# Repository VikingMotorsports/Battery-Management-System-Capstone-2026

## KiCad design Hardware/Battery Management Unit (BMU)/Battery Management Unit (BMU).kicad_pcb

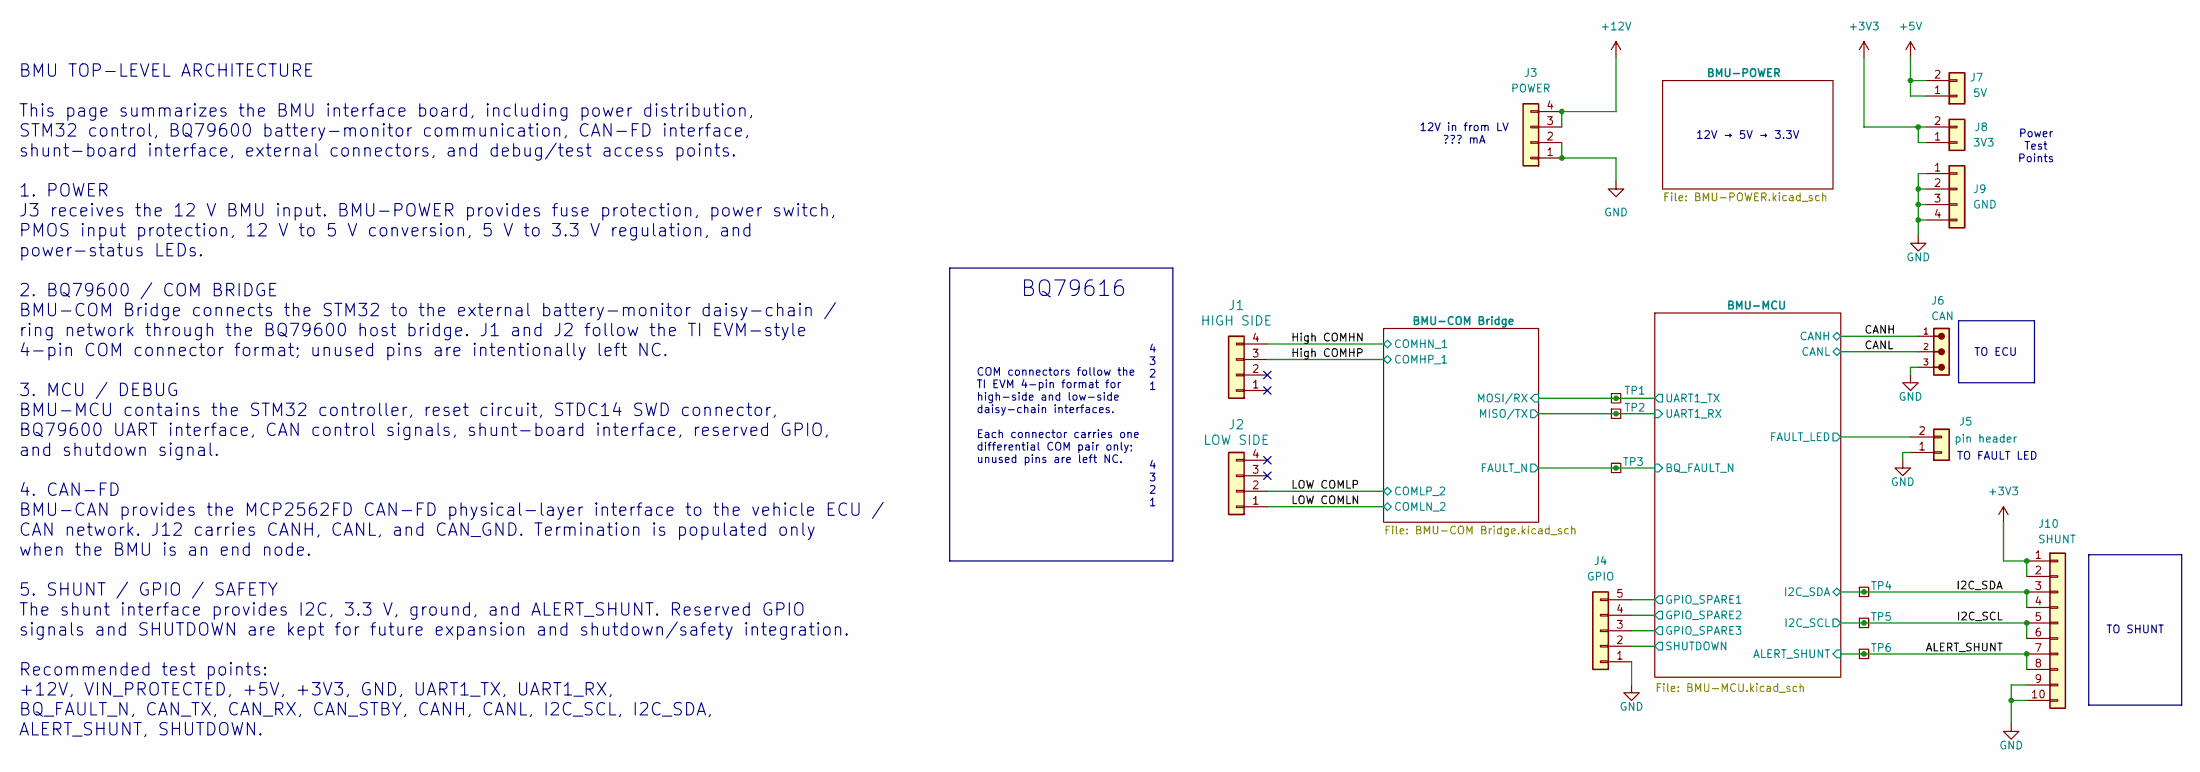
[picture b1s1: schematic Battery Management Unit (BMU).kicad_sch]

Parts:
J1: HIGH SIDE; 705510038; MPN 705510038
J2: LOW SIDE; 705510038; MPN 705510038
J3: POWER; PinHeader_1x04_P2.54mm_Vertical; MPN PRPC004SAAN-RC
J4: GPIO; PinHeader_1x05_P2.54mm_Vertical; MPN PRPC005SAAN-RC
J5: pin header; PinHeader_1x02_P2.54mm_Vertical; MPN PRPC002SAAN-RC
J6: CAN; 691382000003; MPN 691382000003
J7: 5V; PinHeader_1x02_P2.54mm_Vertical; MPN PRPC002SAAN-RC
J8: 3V3; PinHeader_1x02_P2.54mm_Vertical; MPN PRPC002SAAN-RC
J9: GND; PinHeader_1x04_P2.54mm_Vertical; MPN PRPC004SAAN-RC
J10: SHUNT; PinHeader_1x10_P2.54mm_Vertical; MPN PRPC010SAAN-RC
TP1, TP2, TP3, TP4, TP5, TP6: TestPoint_Small; TestPoint_THTPad_D1.5mm_Drill0.7mm

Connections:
+3V3: J8.1, J8.2, J10.1, J10.2; also elsewhere on the board
+5V: J7.1, J7.2; also elsewhere on the board
+12V: J3.3, J3.4; also elsewhere on the board
/ALERT_SHUNT: J10.7, J10.8, TP6.1 (1_1); also elsewhere on the board
/BMU-COM Bridge/FAULT_N: TP3.1 (1_1); also elsewhere on the board
/BMU-COM Bridge/MISO/TX: TP2.1 (1_1); also elsewhere on the board
/BMU-COM Bridge/MOSI/RX: TP1.1 (1_1); also elsewhere on the board
/BMU-MCU/FAULT_LED: J5.2; also elsewhere on the board
/BMU-MCU/GPIO_SPARE1: J4.5; also elsewhere on the board
/BMU-MCU/GPIO_SPARE2: J4.4; also elsewhere on the board
/BMU-MCU/GPIO_SPARE3: J4.3; also elsewhere on the board
/BMU-MCU/SHUTDOWN: J4.2; also elsewhere on the board
/CANH: J6.1; also elsewhere on the board
/CANL: J6.2; also elsewhere on the board
/High COMHN: J1.4; also elsewhere on the board
/High COMHP: J1.3; also elsewhere on the board
/I2C_SCL: J10.5, J10.6, TP5.1 (1_1); also elsewhere on the board
/I2C_SDA: J10.3, J10.4, TP4.1 (1_1); also elsewhere on the board
/LOW COMLN: J2.1; also elsewhere on the board
/LOW COMLP: J2.2; also elsewhere on the board
GND: J3.1, J3.2, J4.1, J5.1, J6.3, J9.1, J9.2, J9.3, J9.4, J10.9, J10.10; also elsewhere on the board

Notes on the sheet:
4 3 2 1
12V in from LV ??? mA
TO FAULT LED
COM connectors follow the TI EVM 4-pin format for high-side and low-side daisy-chain interfaces. Each connector carries one differential COM pair only; unused pins are left NC.
Power Test Points
TO ECU
BMU TOP-LEVEL ARCHITECTURE This page summarizes the BMU interface board, including power distribution, STM32 control, BQ79600 battery-monitor communication, CAN-FD interface, shunt-board interface, external connectors, and debug/test access points. 1. POWER J3 receives the 12 V BMU input. BMU-POWER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
TO SHUNT
12V → 5V → 3.3V
BQ79616

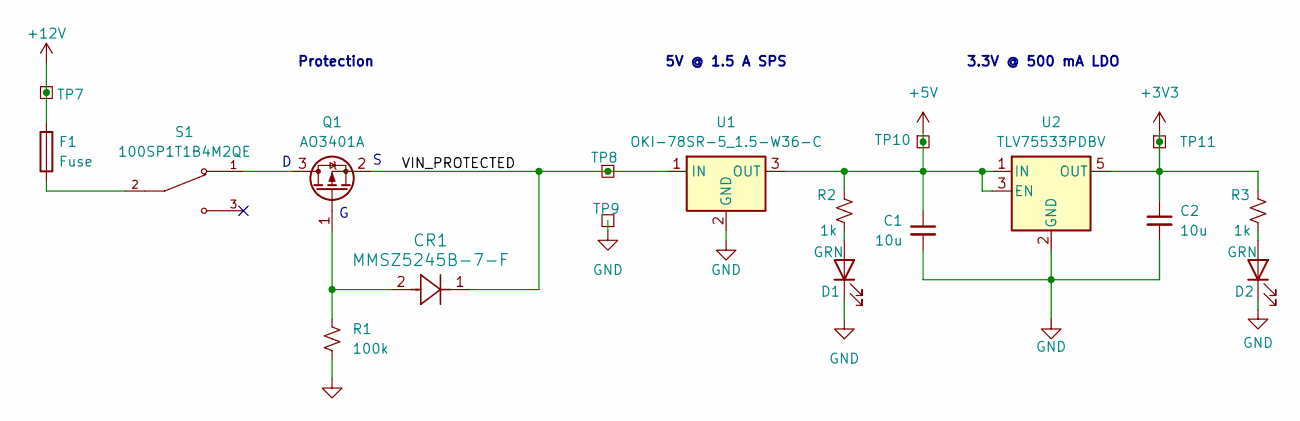
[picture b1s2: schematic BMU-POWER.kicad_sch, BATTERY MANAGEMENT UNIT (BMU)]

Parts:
C1, C2: 10u; C_0805_2012Metric; MPN CC0805KKX5R8BB106
CR1: MMSZ5245B-7-F; SOD123_DIO; MPN MMSZ5245B-7-F
D1, D2: GRN; LED_0805_2012Metric_Pad1.15x1.40mm_HandSolder; MPN LTST-C170GKT
F1: Fuse; Fuse_1206_3216Metric; MPN 0466001.NR
Q1: AO3401A; SOT-23; MPN AO3401A
R1: 100k; R_0805_2012Metric; MPN RC0805FR-07100KL
R2, R3: 1k; R_0805_2012Metric; MPN RC0805FR-071KL
S1: 100SP1T1B4M2QE; SW_100SP1T1B4M2QE; PARTREV E
TP7, TP8, TP9, TP10, TP11: TestPoint_Small; TestPoint_THTPad_D1.5mm_Drill0.7mm
U1: OKI-78SR-5_1.5-W36-C; Converter_DCDC_Murata_OKI-78SR_Vertical; MPN OKI-78SR-5/1.5-W36-C
U2: TLV75533PDBV; SOT-23-5; MPN TLV75533PDBVR

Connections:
+3V3: C2.1, R3.2, TP11.1 (1_1), U2.5 (OUT); also elsewhere on the board
+5V: C1.1, R2.2, TP10.1 (1_1), U1.3 (OUT), U2.1 (IN), U2.3 (EN); also elsewhere on the board
+12V: F1.2, TP7.1 (1_1); also elsewhere on the board
/BMU-POWER/VIN_PROTECTED: CR1.1, Q1.2 (S), TP8.1 (1_1), U1.1 (IN)
GND: C1.2, C2.2, D1.1 (K), D2.1 (K), R1.2, TP9.1 (1_1), U1.2 (GND), U2.2 (GND); also elsewhere on the board
unnamed: D1.2 (A), R2.1
unnamed: D2.2 (A), R3.1
unnamed: F1.1, S1.2
unnamed: Q1.3 (D), S1.1
unnamed: CR1.2, Q1.1 (G), R1.1

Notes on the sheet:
3.3V @ 500 mA LDO
5V @ 1.5 A SPS
Protection

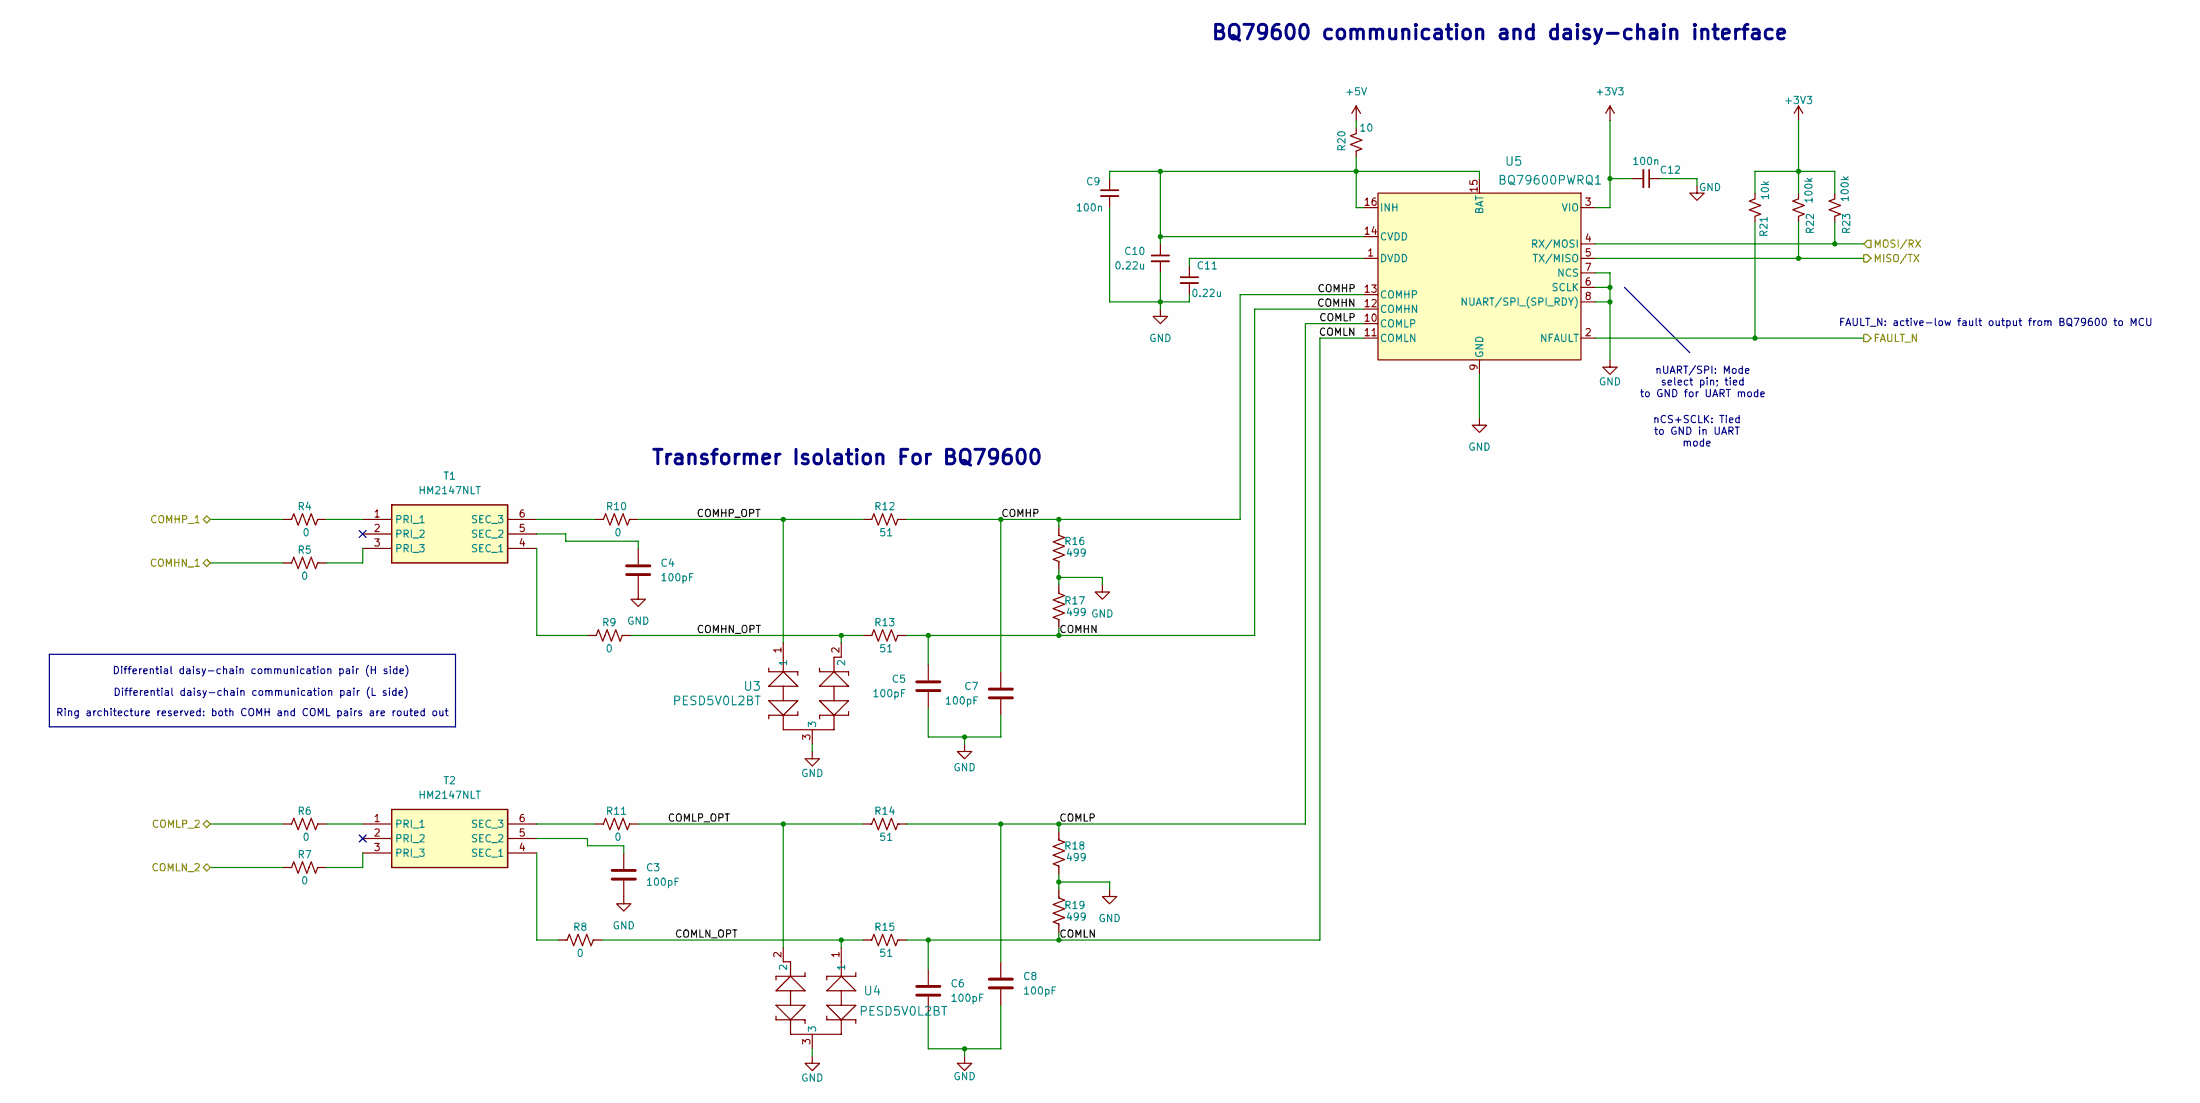
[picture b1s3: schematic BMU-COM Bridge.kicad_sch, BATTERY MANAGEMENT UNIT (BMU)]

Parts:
C3, C4, C5, C6, C7, C8: 100pF; C_0805_2012Metric; MPN CC0805KRNPO9BN101
C9, C12: 100n; C_0805_2012Metric; MPN CC0805KRX7R9BB104
C10, C11: 0.22u; C_0805_2012Metric; MPN CC0805KKX7R9BB224
R4, R5, R6, R7, R8, R9, R10, R11: 0; R_0805_2012Metric; MPN RC0805JR-070RL
R12, R13, R14, R15: 51; R_0805_2012Metric; MPN RC0805FR-0751RL
R16, R17, R18, R19: 499; R_0805_2012Metric; MPN RC0805FR-07499RL
R20: 10; R_0805_2012Metric; MPN RC0805FR-0710RL
R21: 10k; R_0805_2012Metric; MPN RC0805FR-0710KL
R22, R23: 100k; R_0805_2012Metric; MPN RC0805FR-07100KL
T1, T2: HM2147NLT; Manufacturer_Part_Number HM2147NLT; Mouser Part Number 673-HM2147NLT
U3, U4: PESD5V0L2BT; SOT23_NEX; MPN PESD5V0L2BT,215
U5: BQ79600PWRQ1; TSSOP16_PW_TEX; MPN BQ79600PWRQ1

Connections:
+3V3: C12.2, R21.1, R22.1, R23.1, U5.3 (VIO); also elsewhere on the board
+5V: R20.1; also elsewhere on the board
/BMU-COM Bridge/COMHN: C5.1, R13.2, R17.2, U5.12 (COMHN)
/BMU-COM Bridge/COMHN_OPT: R9.2, R13.1, U3.2
/BMU-COM Bridge/COMHP: C7.1, R12.2, R16.1, U5.13 (COMHP)
/BMU-COM Bridge/COMHP_OPT: R10.2, R12.1, U3.1
/BMU-COM Bridge/COMLN: C6.1, R15.2, R19.2, U5.11 (COMLN)
/BMU-COM Bridge/COMLN_OPT: R8.2, R15.1, U4.1
/BMU-COM Bridge/COMLP: C8.1, R14.2, R18.1, U5.10 (COMLP)
/BMU-COM Bridge/COMLP_OPT: R11.2, R14.1, U4.2
/BMU-COM Bridge/FAULT_N: R21.2, U5.2 (NFAULT); also elsewhere on the board
/BMU-COM Bridge/MISO/TX: R22.2, U5.5 (TX/MISO); also elsewhere on the board
/BMU-COM Bridge/MOSI/RX: R23.2, U5.4 (RX/MOSI); also elsewhere on the board
/High COMHN: R5.1; also elsewhere on the board
/High COMHP: R4.1; also elsewhere on the board
/LOW COMLN: R7.1; also elsewhere on the board
/LOW COMLP: R6.1; also elsewhere on the board
GND: C3.2, C4.2, C5.2, C6.2, C7.2, C8.2, C9.2, C10.2, C11.2, C12.1, R16.2, R17.1, R18.2, R19.1, U3.3, U4.3, U5.6 (SCLK), U5.7 (NCS), U5.8 (NUART/SPI_(SPI_RDY)), U5.9 (GND); also elsewhere on the board
unnamed: R4.2, T1.1 (PRI_1)
unnamed: R5.2, T1.3 (PRI_3)
unnamed: R9.1, T1.4 (SEC_1)
unnamed: C4.1, T1.5 (SEC_2)
unnamed: R10.1, T1.6 (SEC_3)
unnamed: R6.2, T2.1 (PRI_1)
unnamed: R7.2, T2.3 (PRI_3)
unnamed: R8.1, T2.4 (SEC_1)
unnamed: C3.1, T2.5 (SEC_2)
unnamed: R11.1, T2.6 (SEC_3)
unnamed: C9.1, C10.1, R20.2, U5.14 (CVDD), U5.15 (BAT), U5.16 (INH)
unnamed: C11.1, U5.1 (DVDD)

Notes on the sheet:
Differential daisy-chain communication pair (H side)
Transformer Isolation For BQ79600
Differential daisy-chain communication pair (L side)
BQ79600 communication and daisy-chain interface
Ring architecture reserved: both COMH and COML pairs are routed out
nUART/SPI: Mode select pin; tied to GND for UART mode
FAULT_N: active-low fault output from BQ79600 to MCU
nCS+SCLK: Tied to GND in UART mode

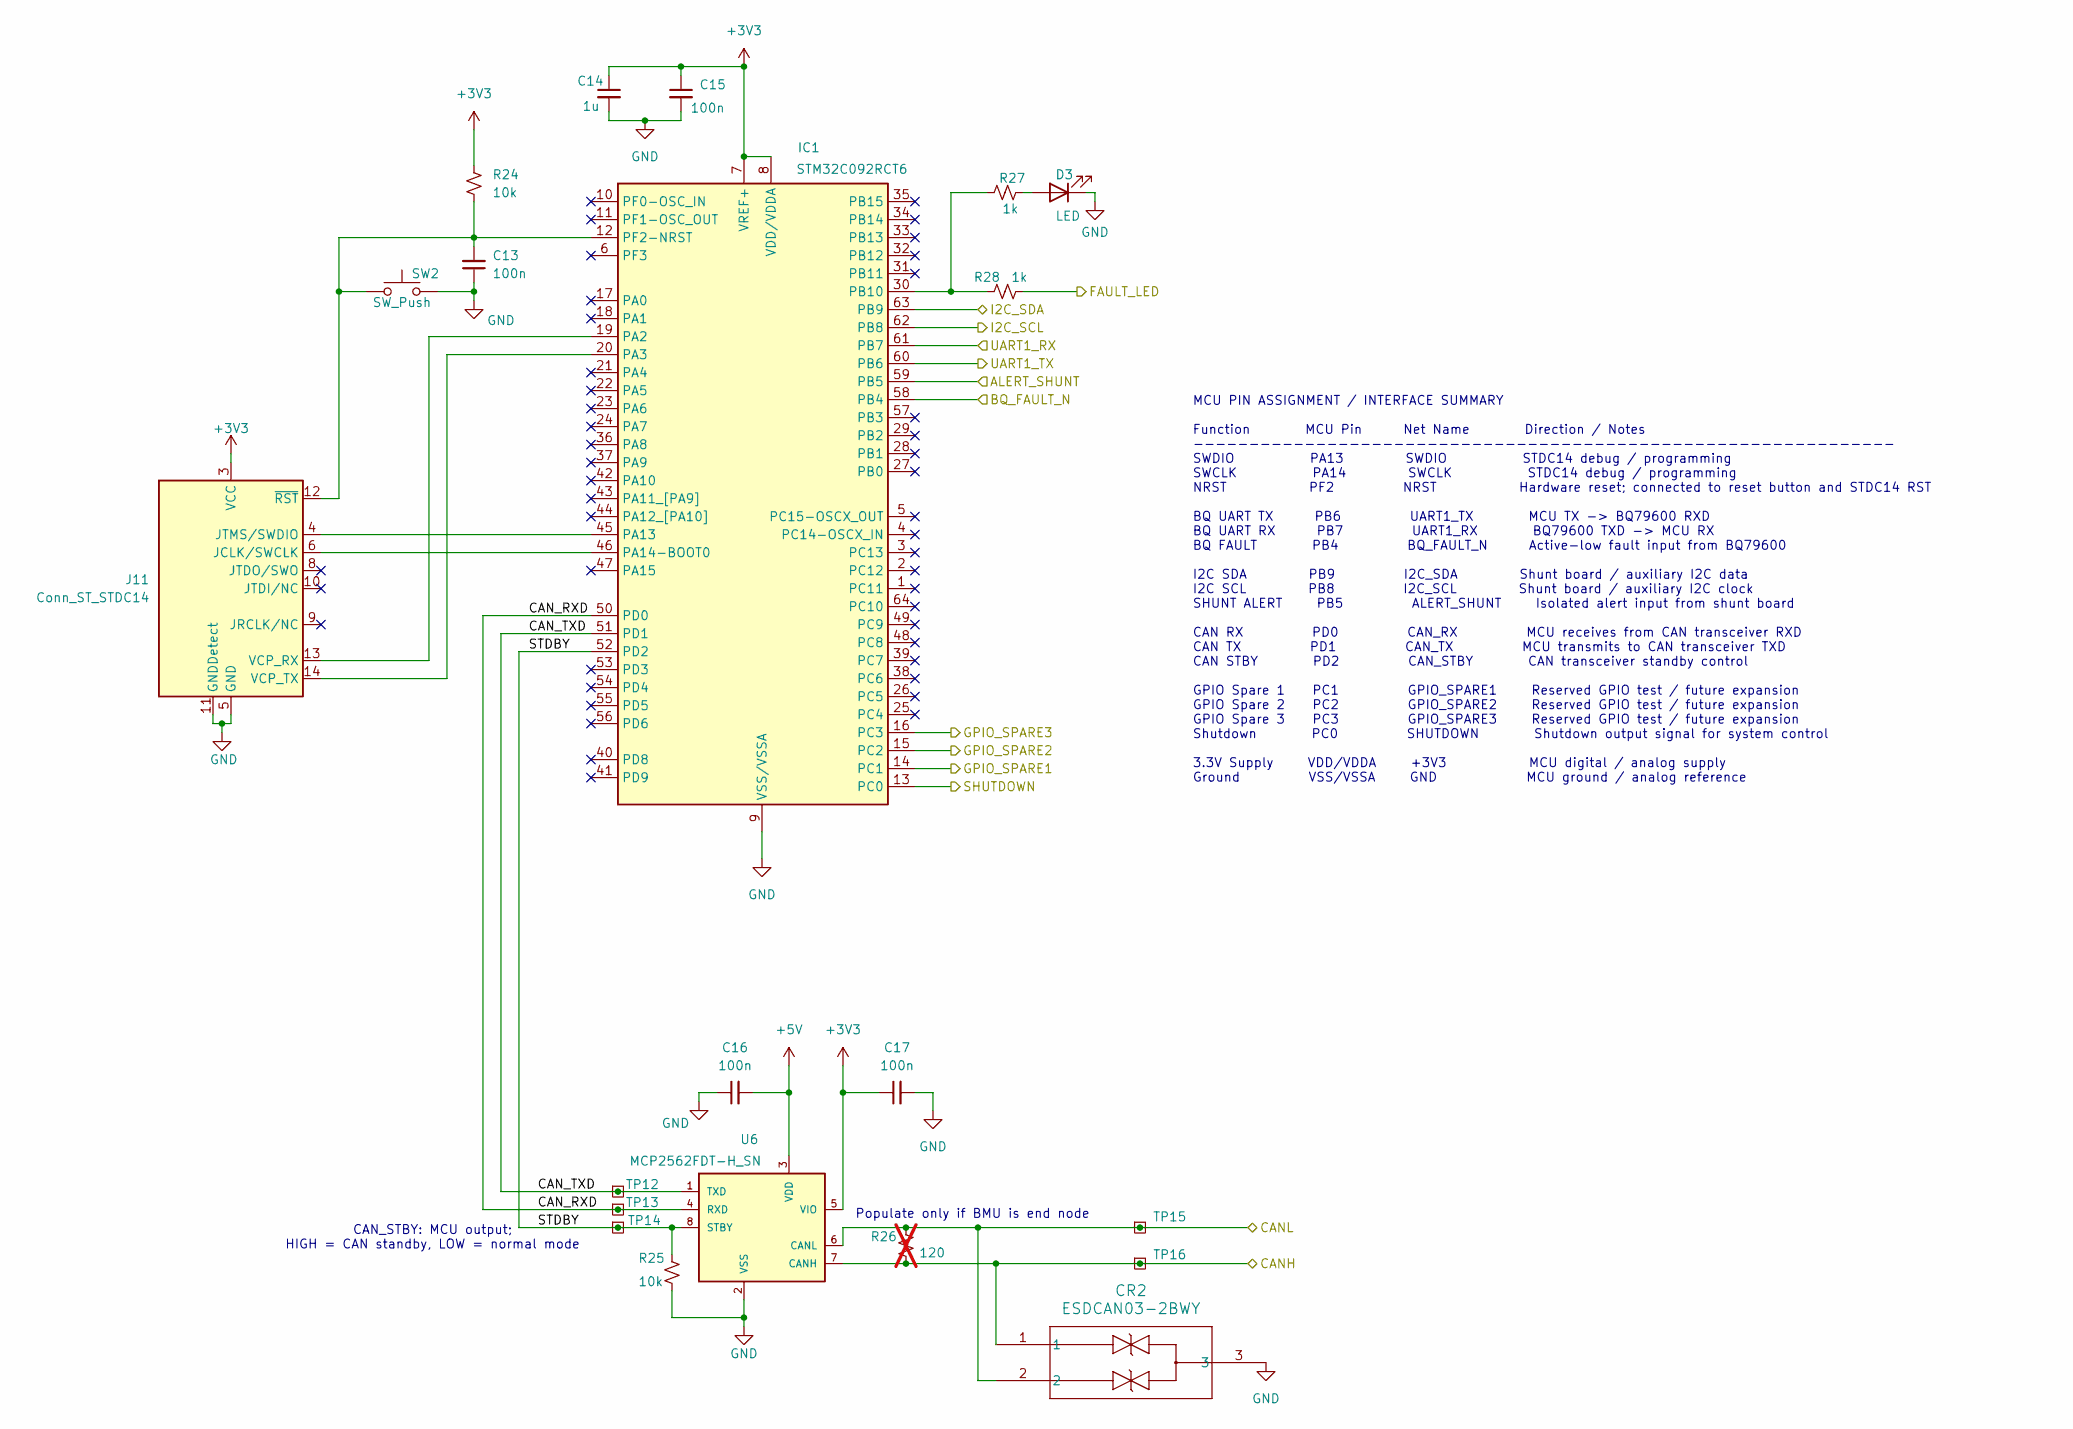
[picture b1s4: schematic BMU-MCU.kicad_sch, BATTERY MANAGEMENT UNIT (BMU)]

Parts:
C13, C15, C16, C17: 100n; C_0805_2012Metric; MPN CC0805KRX7R9BB104
C14: 1u; C_0805_2012Metric; MPN CC0805KKX7R7BB105
CR2: ESDCAN03-2BWY; SOT323-3L_STM; MPN ESDCAN03-2BWY
D3: LED; LED_0805_2012Metric_Pad1.15x1.40mm_HandSolder; MPN LTST-C170KRKT
IC1: STM32C092RCT6; QFP50P1200X1200X160-64N; Manufacturer_Part_Number STM32C092RCT6; Mouser Part Number 511-STM32C092RCT6
J11: Conn_ST_STDC14; PinHeader_2x07_P1.27mm_Vertical; MPN FTSH-107-01-F-DV-K
R24, R25: 10k; R_0805_2012Metric; MPN RC0805FR-0710KL
R26: 120; R_0805_2012Metric; MPN RC0805FR-07120RL; not fitted
R27, R28: 1k; R_0805_2012Metric; MPN RC0805FR-071KL
SW2: SW_Push; SW_PUSH_6mm_H4.3mm; MPN B3F-1000
TP12, TP13, TP14, TP15, TP16: TestPoint_Small; TestPoint_THTPad_D1.5mm_Drill0.7mm
U6: MCP2562FDT-H_SN; SOIC127P600X175-8N; MPN MCP2562FDT-H/SN

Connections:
+3V3: C14.1, C15.1, C17.1, IC1.7 (VREF+), IC1.8 (VDD/VDDA), J11.3 (VCC), R24.1, U6.5 (VIO); also elsewhere on the board
+5V: C16.2, U6.3 (VDD); also elsewhere on the board
/ALERT_SHUNT: IC1.59 (PB5); also elsewhere on the board
/BMU-COM Bridge/FAULT_N: IC1.58 (PB4); also elsewhere on the board
/BMU-COM Bridge/MISO/TX: IC1.61 (PB7); also elsewhere on the board
/BMU-COM Bridge/MOSI/RX: IC1.60 (PB6); also elsewhere on the board
/BMU-MCU/CAN_RXD: IC1.50 (PD0), TP13.1 (1_1), U6.4 (RXD)
/BMU-MCU/CAN_TXD: IC1.51 (PD1), TP12.1 (1_1), U6.1 (TXD)
/BMU-MCU/FAULT_LED: R28.2; also elsewhere on the board
/BMU-MCU/GPIO_SPARE1: IC1.14 (PC1); also elsewhere on the board
/BMU-MCU/GPIO_SPARE2: IC1.15 (PC2); also elsewhere on the board
/BMU-MCU/GPIO_SPARE3: IC1.16 (PC3); also elsewhere on the board
/BMU-MCU/SHUTDOWN: IC1.13 (PC0); also elsewhere on the board
/BMU-MCU/STDBY: IC1.52 (PD2), R25.1, TP14.1 (1_1), U6.8 (STBY)
/CANH: CR2.1, R26.2, TP16.1 (1_1), U6.7 (CANH); also elsewhere on the board
/CANL: CR2.2, R26.1, TP15.1 (1_1), U6.6 (CANL); also elsewhere on the board
/I2C_SCL: IC1.62 (PB8); also elsewhere on the board
/I2C_SDA: IC1.63 (PB9); also elsewhere on the board
GND: C13.1, C14.2, C15.2, C16.1, C17.2, CR2.3, D3.1 (K), IC1.9 (VSS/VSSA), J11.5 (GND), J11.7 (GND), J11.11 (GNDDetect), R25.2, SW2.2, U6.2 (VSS); also elsewhere on the board
unnamed: D3.2 (A), R27.2
unnamed: IC1.19 (PA2), J11.13 (VCP_RX)
unnamed: IC1.20 (PA3), J11.14 (VCP_TX)
unnamed: IC1.45 (PA13), J11.4 (JTMS/SWDIO)
unnamed: IC1.46 (PA14-BOOT0), J11.6 (JCLK/SWCLK)
unnamed: IC1.30 (PB10), R27.1, R28.1
unnamed: C13.2, IC1.12 (PF2-NRST), J11.12 (~RST), R24.2, SW2.1

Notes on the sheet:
MCU PIN ASSIGNMENT / INTERFACE SUMMARY Function MCU Pin Net Name Direction / Notes --------------------------------------------------------------- SWDIO PA13 SWDIO STDC14 debug / programming SWCLK PA14 SWCLK STDC14 debug / programming NRST PF2 NRST Hardware reset; connected to reset button and STDC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
CAN_STBY: MCU output; HIGH = CAN standby, LOW = normal mode
Populate only if BMU is end node

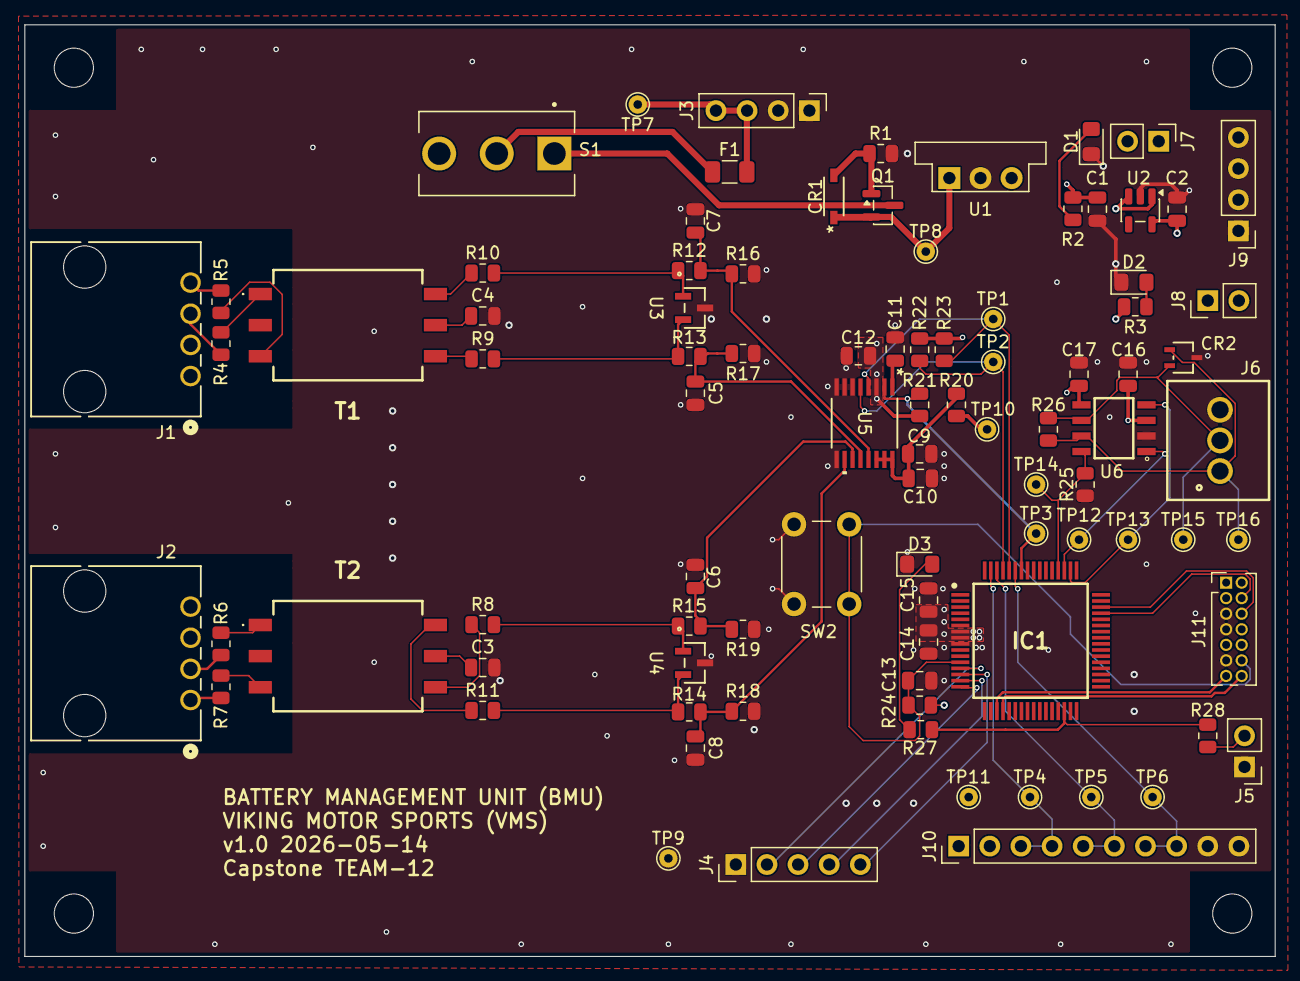
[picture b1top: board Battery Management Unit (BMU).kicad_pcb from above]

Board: 4 copper layers, 102.0 x 76.0 mm, 90 parts (0 on the bottom side), 57 nets.

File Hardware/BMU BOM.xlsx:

BMU BOM
Item | Reference | Qty | Value / Part Number | Footprint / Package | Description | Manufacturer / MPN | Supplier | Notes | Link
1 | C1, C2 | 2 | 10uF | C_0805_2012Metric | Capacitor, SMD 0805 | TBD | Lab Stock / Digi-Key / Mouser | Common capacitor
2 | C3, C4, C5, C6, C7, C8 | 6 | 100pF | C_0805_2012Metric | Capacitor, SMD 0805 | TBD | Lab Stock / Digi-Key / Mouser | Common capacitor
3 | C9, C12, C13, C15, C16, C17 | 6 | 0.1uF / 100nF | C_0805_2012Metric | Capacitor, SMD 0805 | TBD | Lab Stock / Digi-Key / Mouser | Common decoupling capacitor
4 | C10, C11 | 2 | 0.22uF | C_0805_2012Metric | Capacitor, SMD 0805 | TBD | Lab Stock / Digi-Key / Mouser | Common capacitor
5 | C14 | 1 | 1uF | C_0805_2012Metric | Capacitor, SMD 0805 | TBD | Lab Stock / Digi-Key / Mouser | Common capacitor
6 | CR1 | 1 | MMSZ5245B-7-F | SOD123_DIO | Zener diode | MMSZ5245B-7-F | Digi-Key / Mouser | Protection diode
7 | CR2 | 1 | ESDCAN03-2BWY | SOT323-3L_STM | CAN ESD protection diode | ESDCAN03-2BWY | Digi-Key / Mouser | CAN protection
8 | D1, D2 | 2 | GRN | LED_0805_2012Metric_Pad1.15x1.40mm_HandSolder | Green LED, SMD 0805 | TBD | Digi-Key / Mouser | Status LED
9 | D3 | 1 | LED | LED_0805_2012Metric_Pad1.15x1.40mm_HandSolder | LED, SMD 0805 | TBD | Digi-Key / Mouser | Status LED
10 | F1 | 1 | Fuse | Fuse_1206_3216Metric | Fuse, SMD 1206 | TBD | Digi-Key / Mouser | Input protection fuse
11 | IC1 | 1 | STM32C092RCT6 | QFP50P1200X1200X160-64N | STM32 microcontroller | STM32C092RCT6 | Digi-Key / Mouser | Main MCU
12 | J1, J2 | 2 | 705510038 | 705510038 | High-side / low-side connector | 705510038 | Digi-Key / Mouser | External COM connectors
13 | J3 | 1 | POWER | PinHeader_1x04_P2.54mm_Vertical | Power pin header | TBD | Digi-Key / Mouser | 12V input / GND
14 | J4 | 1 | GPIO | PinHeader_1x05_P2.54mm_Vertical | GPIO pin header | TBD | Digi-Key / Mouser | GPIO spare / shutdown
15 | J5, J7, J8 | 3 | pin header / 5V / 3V3 | PinHeader_1x02_P2.54mm_Vertical | 2-pin header | TBD | Digi-Key / Mouser | Fault LED / 5V / 3V3 headers
16 | J6 | 1 | 69138200003 | 69138200003 | CAN connector | 69138200003 | Digi-Key / Mouser | To ECU CAN interface
17 | J9 | 1 | GND | PinHeader_1x04_P2.54mm_Vertical | GND pin header | TBD | Digi-Key / Mouser | Ground test / access header
18 | J10 | 1 | SHUNT | PinHeader_1x10_P2.54mm_Vertical | Shunt connector header | TBD | Digi-Key / Mouser | 3V3 / I2C / ALERT / GND
19 | J11 | 1 | Conn_ST_STDC14 | PinHeader_2x07_P1.27mm | STDC14 SWD debug connector | TBD | Digi-Key / Mouser | MCU programming/debug
20 | Q1 | 1 | DMP3099L | SOT-23 | P-channel MOSFET | DMP3099L | Digi-Key / Mouser | Power path / protection
21 | R1, R22, R23 | 3 | 100kΩ | R_0805_2012Metric | Resistor, SMD 0805 | TBD | Lab Stock / Digi-Key / Mouser | Common resistor
22 | R2, R3, R27, R28 | 4 | 1kΩ | R_0805_2012Metric | Resistor, SMD 0805 | TBD | Lab Stock / Digi-Key / Mouser | Common resistor
23 | R4, R5, R6, R7, R8, R9, R10, R11 | 8 | 0Ω | R_0805_2012Metric | 0-ohm resistor / jumper | TBD | Lab Stock / Digi-Key / Mouser | Configuration jumper
24 | R12, R13, R14, R15 | 4 | 51Ω | R_0805_2012Metric | Resistor, SMD 0805 | TBD | Lab Stock / Digi-Key / Mouser | Common resistor
25 | R16, R17, R18, R19 | 4 | 499Ω | R_0805_2012Metric | Resistor, SMD 0805 | TBD | Lab Stock / Digi-Key / Mouser | Common resistor
26 | R20 | 1 | 10Ω | R_0805_2012Metric | Resistor, SMD 0805 | TBD | Lab Stock / Digi-Key / Mouser | Common resistor
27 | R21, R24, R25 | 3 | 10kΩ | R_0805_2012Metric | Resistor, SMD 0805 | TBD | Lab Stock / Digi-Key / Mouser | Common resistor
28 | R26 | 1 | 120Ω | R_0805_2012Metric | CAN termination resistor | TBD | Lab Stock / Digi-Key / Mouser | CAN termination
29 | SW1 | 1 | Power Switch | SW_DIP_SPSTx01_Slide_9.78x4.72mm_W7.62mm_P2.54mm | Slide power switch | TBD | Digi-Key / Mouser | Power switch
30 | SW2 | 1 | SW_Push | SW_PUSH_6mm_H4.3mm | Push button switch | TBD | Digi-Key / Mouser | Reset / user button
31 | T1, T2 | 2 | CEP99-102 | CEP99102 | Transformer / isolation component | CEP99-102 | Digi-Key / Mouser | Verify exact function from schematic
32 | U1 | 1 | OKI-78SR-5_1.5-W36-C | Converter_DCDC_Murata_OKI-78SR_Vertical | DC-DC converter module | OKI-78SR-5/1.5-W36-C | Digi-Key / Mouser | 12V to 5V converter
33 | U2 | 1 | TLV75533PDBV | SOT-23-5 | 3.3V linear regulator | TLV75533PDBV | Digi-Key / Mouser | 5V to 3.3V regulator
34 | U3, U4 | 2 | PESD5V0L2BT | SOT23_NEX | ESD protection diode | PESD5V0L2BT | Digi-Key / Mouser | Signal protection
35 | U5 | 1 | BQ79600PWRQ1 | TSSOP16_PW_TEX | Battery communication bridge IC | BQ79600PWRQ1 | Digi-Key / Mouser | BQ communication bridge
36 | U6 | 1 | MCP2562FDT-H_SN | SOIC127P600X175-8N | CAN transceiver | MCP2562FDT-H/SN | Digi-Key / Mouser | CAN interface

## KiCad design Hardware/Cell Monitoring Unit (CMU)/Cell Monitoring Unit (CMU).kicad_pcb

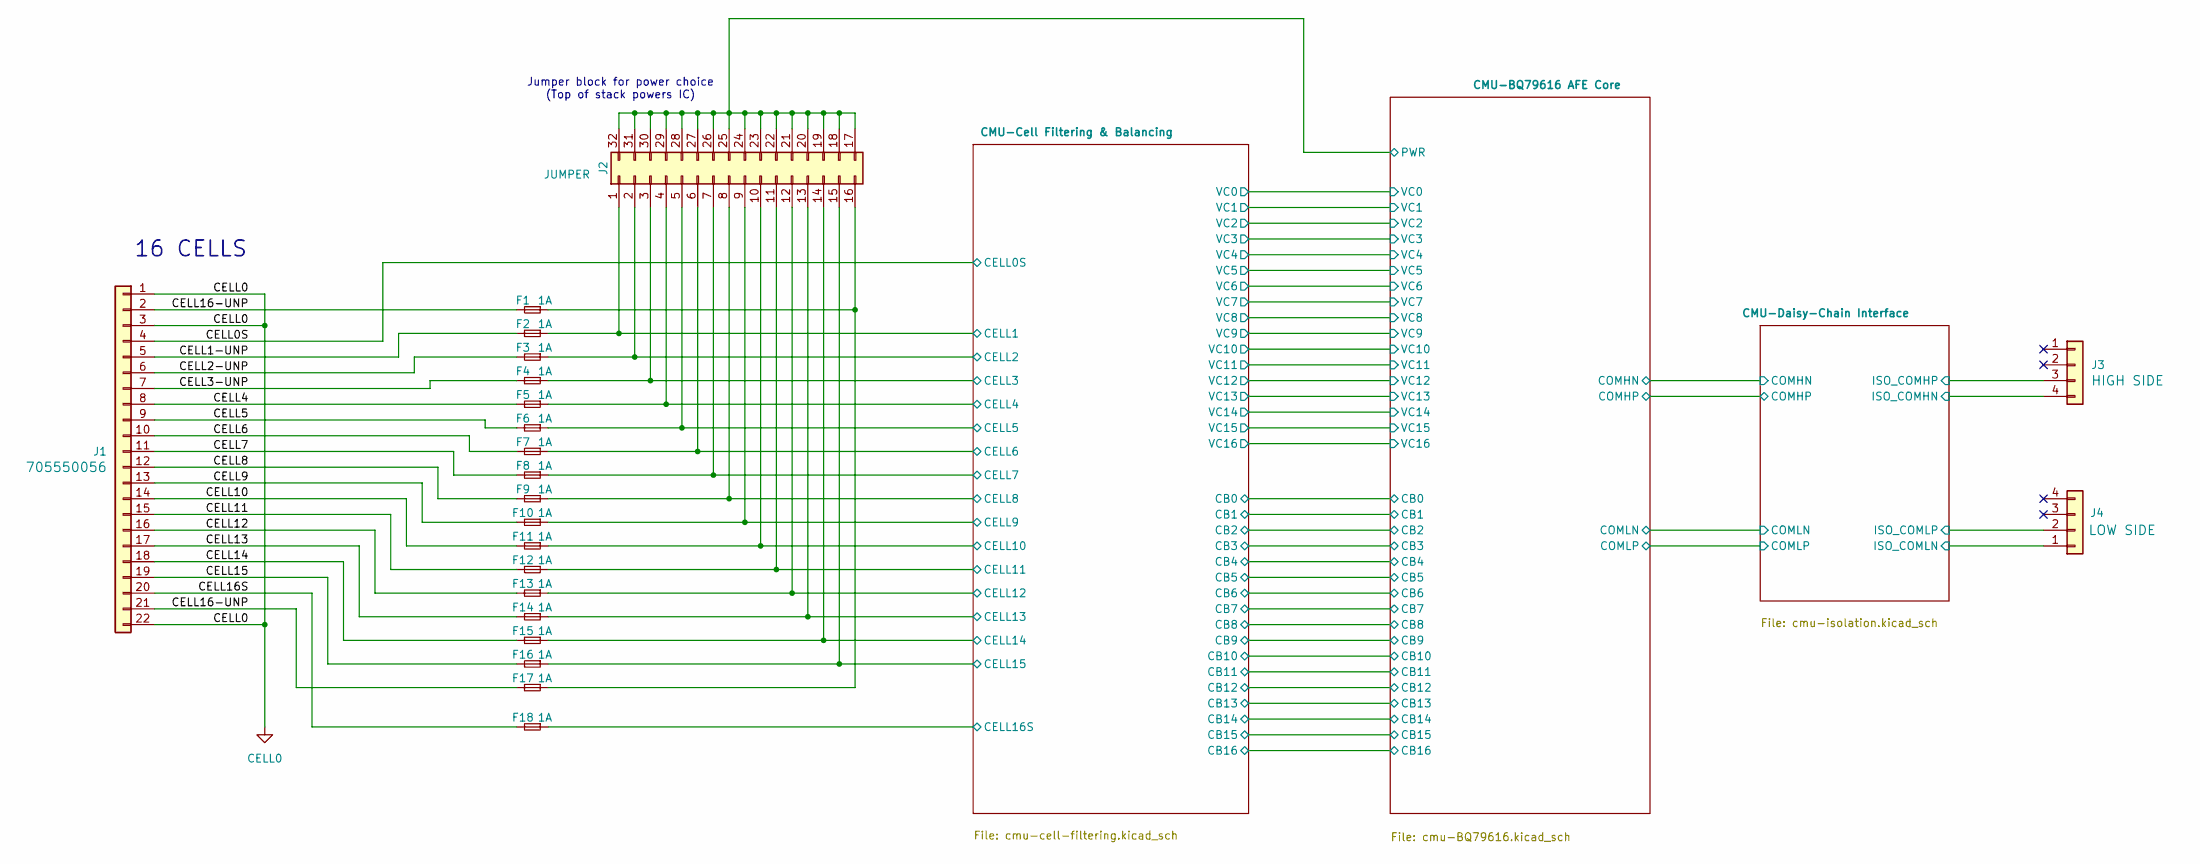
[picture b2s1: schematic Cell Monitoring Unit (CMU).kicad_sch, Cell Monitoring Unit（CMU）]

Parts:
F1, F2, F3, F4, F5, F6, F7, F8, F9, F10, F11, F12, F13, F14, F15, F16, F17, F18: 1A; Fuse_0805_2012Metric; MPN F0805B1R00FSTR
J1: 705550056; MPN 70555-0056
J2: JUMPER; PinHeader_2x16_P2.54mm_Vertical; MPN TSW-116-07-G-D
J3: HIGH SIDE; 705510038; MPN 705510038
J4: LOW SIDE; 705510038; MPN 705510038

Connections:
/CELL0S: J1.4; also elsewhere on the board
/CELL1-UNP: F2.2, J1.5
/CELL2-UNP: F3.2, J1.6
/CELL3-UNP: F4.2, J1.7
/CELL4: F5.2, J1.8
/CELL5: F6.2, J1.9
/CELL6: F7.2, J1.10
/CELL7: F8.2, J1.11
/CELL8: F9.2, J1.12
/CELL9: F10.2, J1.13
/CELL10: F11.2, J1.14
/CELL11: F12.2, J1.15
/CELL12: F13.2, J1.16
/CELL13: F14.2, J1.17
/CELL14: F15.2, J1.18
/CELL15: F16.2, J1.19
/CELL16-UNP: F1.2, F17.2, J1.2, J1.21
/CELL16S: F18.2, J1.20
/CMU-BQ79616 AFE Core/PWR: J2.17, J2.18, J2.19, J2.20, J2.21, J2.22, J2.23, J2.24, J2.25, J2.26, J2.27, J2.28, J2.29, J2.30, J2.31, J2.32; also elsewhere on the board
/CMU-Cell Filtering & Balancing/CELL1: F2.1, J2.1; also elsewhere on the board
/CMU-Cell Filtering & Balancing/CELL2: F3.1, J2.2; also elsewhere on the board
/CMU-Cell Filtering & Balancing/CELL3: F4.1, J2.3; also elsewhere on the board
/CMU-Cell Filtering & Balancing/CELL4: F5.1, J2.4; also elsewhere on the board
/CMU-Cell Filtering & Balancing/CELL5: F6.1, J2.5; also elsewhere on the board
/CMU-Cell Filtering & Balancing/CELL6: F7.1, J2.6; also elsewhere on the board
/CMU-Cell Filtering & Balancing/CELL7: F8.1, J2.7; also elsewhere on the board
/CMU-Cell Filtering & Balancing/CELL8: F9.1, J2.8; also elsewhere on the board
/CMU-Cell Filtering & Balancing/CELL9: F10.1, J2.9; also elsewhere on the board
/CMU-Cell Filtering & Balancing/CELL10: F11.1, J2.10; also elsewhere on the board
/CMU-Cell Filtering & Balancing/CELL11: F12.1, J2.11; also elsewhere on the board
/CMU-Cell Filtering & Balancing/CELL12: F13.1, J2.12; also elsewhere on the board
/CMU-Cell Filtering & Balancing/CELL13: F14.1, J2.13; also elsewhere on the board
/CMU-Cell Filtering & Balancing/CELL14: F15.1, J2.14; also elsewhere on the board
/CMU-Cell Filtering & Balancing/CELL15: F16.1, J2.15; also elsewhere on the board
/CMU-Cell Filtering & Balancing/CELL16S: F18.1; also elsewhere on the board
/CMU-Daisy-Chain Interface/ISO_COMHN: J3.4; also elsewhere on the board
/CMU-Daisy-Chain Interface/ISO_COMHP: J3.3; also elsewhere on the board
/CMU-Daisy-Chain Interface/ISO_COMLN: J4.1; also elsewhere on the board
/CMU-Daisy-Chain Interface/ISO_COMLP: J4.2; also elsewhere on the board
CELL0: J1.1, J1.3, J1.22; also elsewhere on the board
unnamed: F1.1, F17.1, J2.16

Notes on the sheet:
Jumper block for power choice (Top of stack powers IC)
16 CELLS
